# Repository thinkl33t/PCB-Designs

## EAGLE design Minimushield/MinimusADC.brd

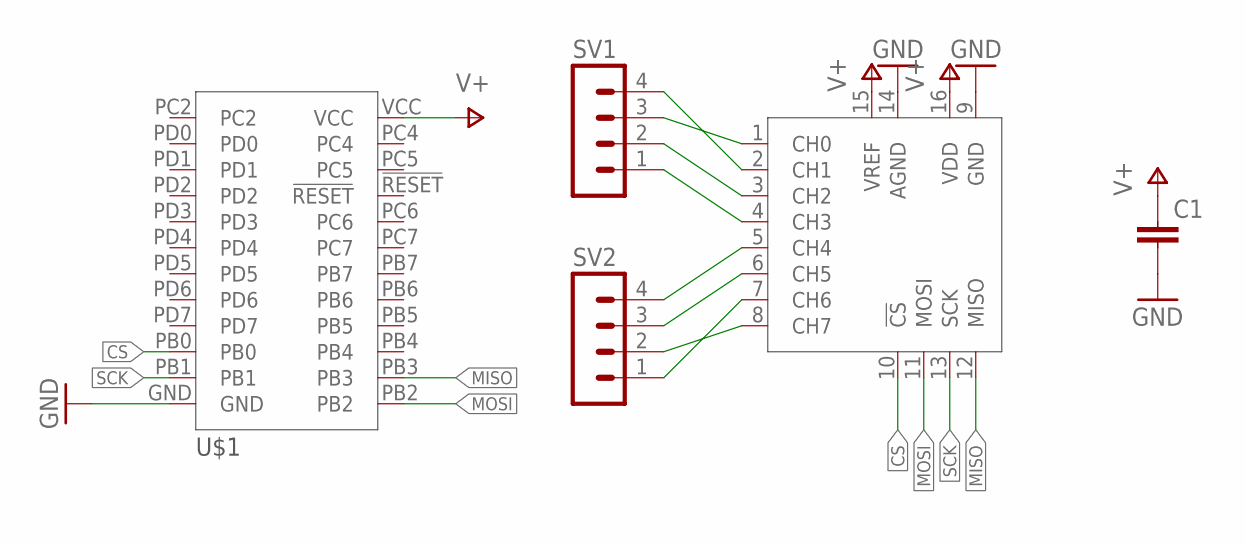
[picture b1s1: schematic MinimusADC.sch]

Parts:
C1: C-EUC0805; C0805
SV1, SV2: MA04-1
U$1: MINIMUSNODIM; MINIMUSNOPINS
U$2: MCP3008SL; SO16

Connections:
CH0: SV1.3, U$2.1 (CH0)
CH1: SV1.4, U$2.2 (CH1)
CH2: SV1.2, U$2.3 (CH2)
CH3: SV1.1, U$2.4 (CH3)
CH4: SV2.4, U$2.5 (CH4)
CH5: SV2.3, U$2.6 (CH5)
CH6: SV2.1, U$2.7 (CH6)
CH7: SV2.2, U$2.8 (CH7)
CS: U$1.PB0, U$2.10 (!CS)
GND: C1.2, U$1.GND, U$2.9 (GND), U$2.14 (AGND)
MISO: U$1.PB3, U$2.12 (MISO)
MOSI: U$1.PB2, U$2.11 (MOSI)
SCK: U$1.PB1, U$2.13 (SCK)
V+: C1.1, U$1.VCC, U$2.15 (VREF), U$2.16 (VDD)

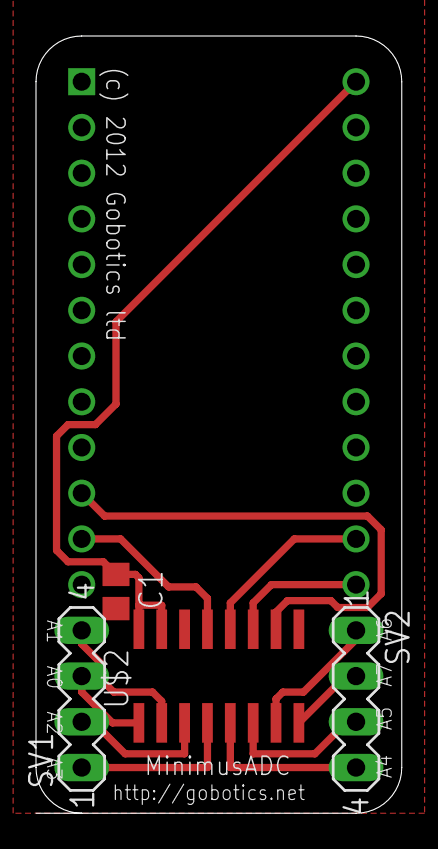
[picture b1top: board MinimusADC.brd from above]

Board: 2 copper layers, 20.3 x 43.2 mm, 5 parts (0 on the bottom side), 14 nets.

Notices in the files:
Minimushield/MinimusADC.brd:
(c) 2012 Gobotics ltd
